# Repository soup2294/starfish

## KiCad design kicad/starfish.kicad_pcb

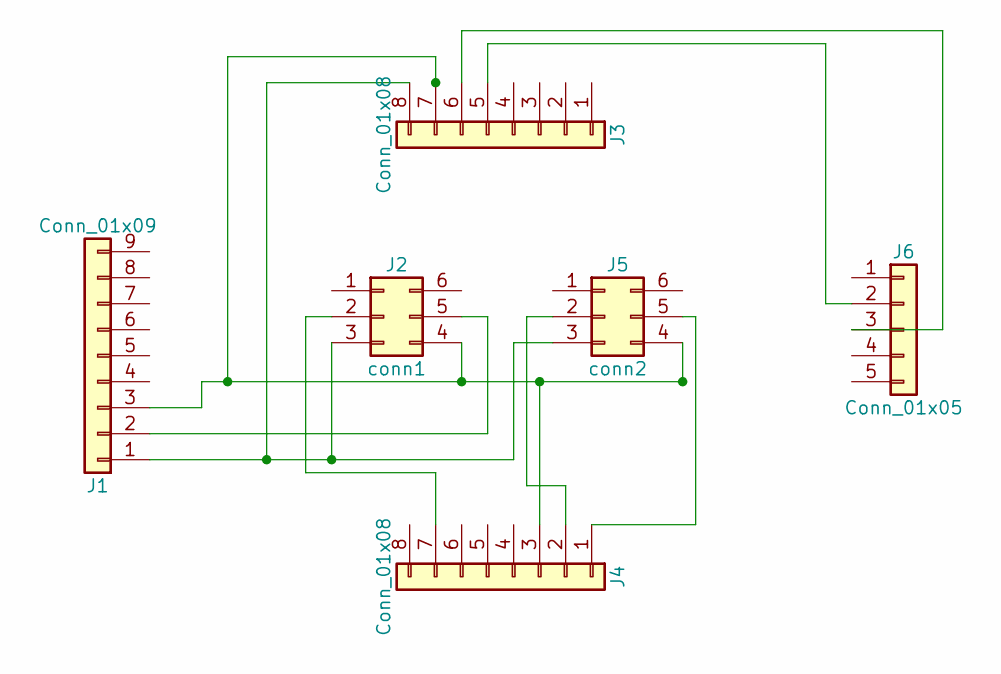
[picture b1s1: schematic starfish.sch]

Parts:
J1: Conn_01x09; Pin_Header_Straight_1x09_Pitch2.54mm
J2: conn1; Pin_Header_Straight_2x03_Pitch2.54mm
J3, J4: Conn_01x08; Pin_Header_Straight_1x08_Pitch2.54mm
J5: conn2; Pin_Header_Straight_2x03_Pitch2.54mm
J6: Conn_01x05; Pin_Header_Straight_1x05_Pitch2.54mm

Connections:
unnamed: J1.1, J2.3, J3.8, J5.3
unnamed: J1.2, J2.5
unnamed: J1.3, J2.4, J3.7, J4.3, J5.4
unnamed: J2.2, J4.7
unnamed: J3.5, J6.2
unnamed: J3.6, J6.3
unnamed: J4.1, J5.5
unnamed: J4.2, J5.2

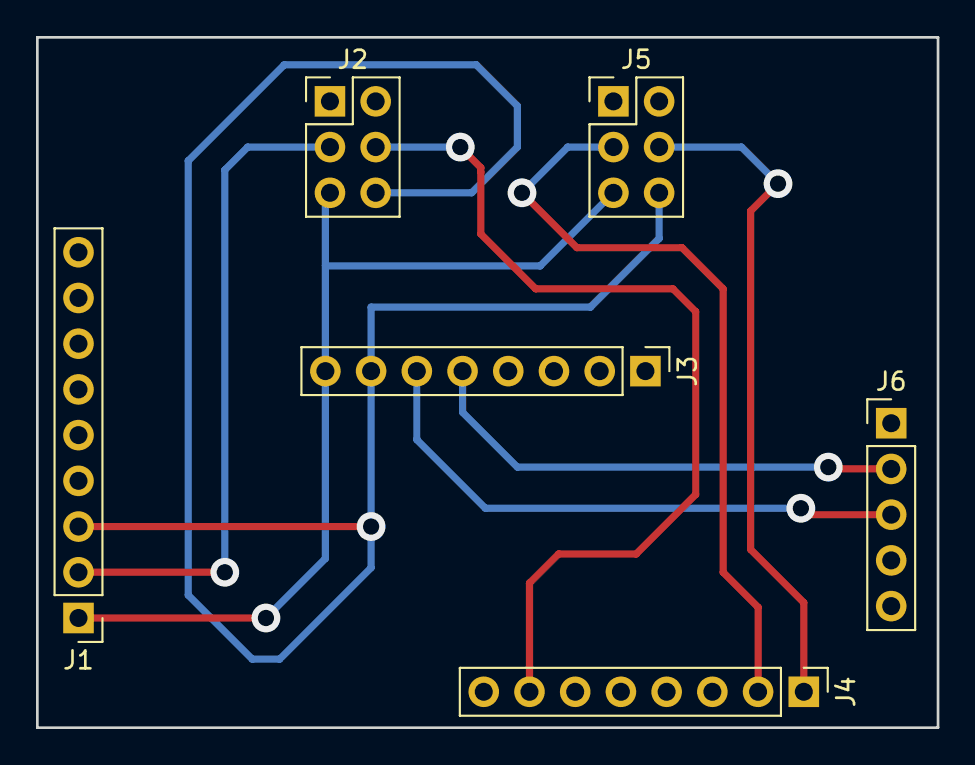
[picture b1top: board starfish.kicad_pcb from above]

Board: 2 copper layers, 50.0 x 38.4 mm, 6 parts (0 on the bottom side), 8 nets.

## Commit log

2018-03-11 Potentiometer
2018-03-18 backup
2018-04-10 kicad
2018-04-17 sensor board double output update
2018-04-18 shield
